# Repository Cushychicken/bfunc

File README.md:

# bfunc - An open source, breadboard friendly function generator

These are the source files for bfunc, a function generator I've been desiging, building, and programming in my spare time. 

The fastest way to understand what's going on here is to read [the design document](http://cushychicken.github.io/bfunc-design-doc/). That should give you a good top-level understanding of this project. If it doesn't, there's a Contact link on my blog. I encourage you to let me know if there's something you don't understand, or is otherwise unclear!

## Project Structure

All hardware files can be found in the `hardware/` directory. All hardware design was done using KiCAD. 

Software is broken into two directories: 

* `sw_embedded/` for all the code running on the bFunc board, and
* `sw_desktop/`, which contains the Python app for the GUI. 

The sw_embedded directory contains two subfolders:

* `stm32_cube_bfunc/` contains all the software used for building the prototype, which I made out of a STM32 BluePill board and a SparkFun Minigen Pro shield. 
* `bfunc_rev1/` contains all the software used in the first board revision. 

## Building the Project

This project uses GitHub Actions for automated building of the embedded firmware. The build process includes:

- **STM32F0 Firmware**: Builds the bfunc_rev1 firmware using ARM GCC toolchain
- **STM32F1 Firmware**: Builds the stm32_cube_bfunc firmware using ARM GCC toolchain

### Local Development

To build the embedded firmware locally, you'll need:

- ARM GCC toolchain for embedded development

Build commands:
```bash
# STM32F0 firmware
cd sw_embedded/bfunc_rev1
make clean
make all

# STM32F1 firmware  
cd sw_embedded/stm32_cube_bfunc
make clean
make all
```

## How can I contribute? 

I'm so glad you asked! Check out the [Call for Users](http://cushychicken.github.io/bfunc-call-for-users/) page on my blog. That will outline the next steps for getting a board, and getting yourself set up to work on it. 

After all that, if you _still_ can't get enough bFunc in your life - I've been keeping weekly project journals on my blog in addition to the design document. Here is a [link to the first one](http://cushychicken.github.io/bfunc-weekone-log/) to get you started.

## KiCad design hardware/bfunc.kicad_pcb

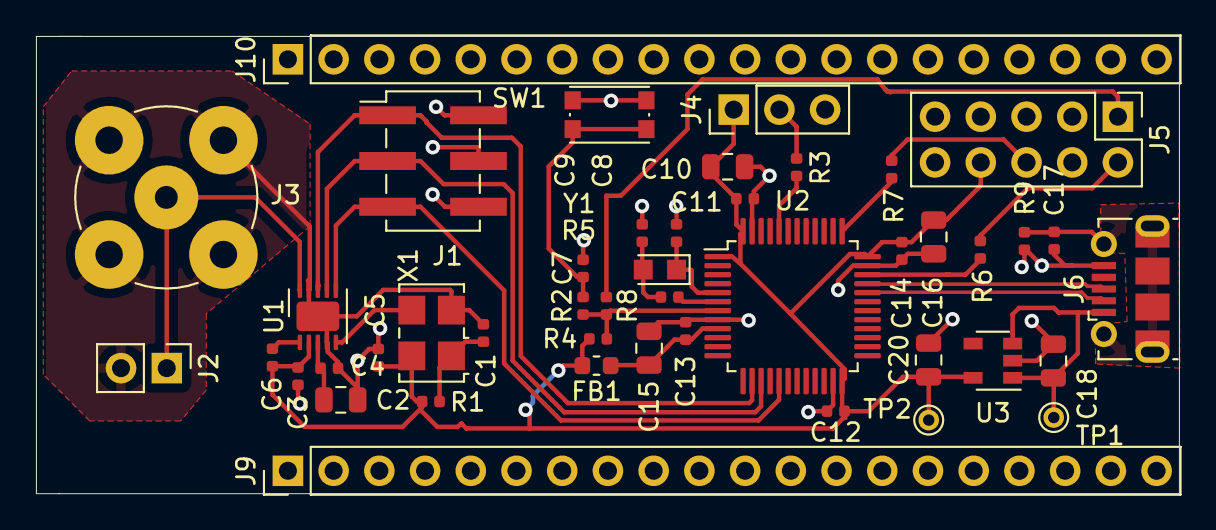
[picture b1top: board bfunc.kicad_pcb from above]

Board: 2 copper layers, 63.5 x 25.4 mm, 45 parts (0 on the bottom side), 27 nets.

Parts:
C1, C3, C4, C5, C11, C12, C14: 100nF; C_0402_1005Metric
C2: 10uF; C_0805_2012Metric
C6, C13: 10nF; C_0402_1005Metric
C7: 100pF; C_0402_1005Metric
C8, C9: 10pF; C_0402_1005Metric
C10, C16: 4.7uF; C_0805_2012Metric
C15, C18, C20: 1uF; C_0805_2012Metric
C17: 4.5nF; C_0402_1005Metric
FB1: Ferrite_Bead; L_0603_1608Metric
J1: Conn_02x03_Odd_Even; PinHeader_2x03_P2.54mm_Vertical_SMD
J2: Conn_01x02_Male; PinHeader_1x02_P2.54mm_Vertical
J3: Conn_Coaxial; BNC_TEConnectivity_1478204_Vertical
J4: Conn_01x03_Male; PinHeader_1x03_P2.54mm_Vertical
J5: Conn_02x05_Odd_Even; PinHeader_2x05_P2.54mm_Vertical
J6: USB_B_Micro; USB_Micro-B_Molex-105017-0001
J9, J10: Conn_01x20_Male; PinHeader_1x20_P2.54mm_Vertical
R1, R3: 10k; R_0402_1005Metric
R2: 330R; R_0402_1005Metric
R4: 2.2K; R_0402_1005Metric
R5: 390R; R_0402_1005Metric
R6, R7, R8: 0R; R_0402_1005Metric
R9: 1M; R_0402_1005Metric
SW1: SW_Push; SW_Push_1P1T_NO_CK_KMR2
TP1, TP2: TestPoint; PINTST
U1: AD9837; LFCSP-WD-10-1EP_3x3mm_P0.5mm_EP1.64x2.38mm
U2: STM32F072C8Tx; LQFP-48_7x7mm_P0.5mm
U3: MIC5504-3.3YM5; SOT-23-5
X1: SG-5032CAN; Oscillator_SMD_SeikoEpson_SG8002LB-4pin_5.0x3.2mm
Y1: Crystal; Crystal_SMD_TXC_9HT11-2pin_2.0x1.2mm_HandSoldering

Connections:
+3.3VA: C13.1, C15.1, FB1.1, U2.9
+3V3: C3.1, C5.1, C6.2, C10.1, C11.1, C12.1, C14.1, C16.1, C20.1, FB1.2, J4.1, J5.8, R1.1, R4.1, TP2.1, U1.2, U2.1, U2.24, U2.36, U2.48, U3.5, X1.4
+5V: C18.1, J6.1, TP1.1, U3.1, U3.3
/DDS Chip/AD9837_COMP: C6.1, U1.1
/DDS Chip/DDS_FSYNC: J1.1, U1.8, U2.14
/DDS Chip/DDS_MCLK: U1.5, X1.3
/DDS Chip/DDS_SCLK: J1.3, U1.7, U2.15
/DDS Chip/DDS_SDATA: J1.5, U1.6, U2.17
/DDS Chip/DDS_VCAP: C2.1, C4.1, U1.3
/DDS Chip/DDS_VOUT: J2.1, J3.1, U1.10
/DDS Chip/OSC_EN: C1.1, R1.2, X1.1
/MCU/BOOT_SW: R3.1, U2.44
/MCU/BOOT_SW_SEL: J4.2, R3.2
/MCU/OSC_IN: C8.1, U2.5, Y1.1
/MCU/OSC_OUT: R5.1, U2.6
/MCU/RESET_L: R2.1, R4.2, R8.2, U2.7
/MCU/RST_L_FLT: J5.1, R8.1
/MCU/SWCLK: R7.2, U2.37
/MCU/SWCLK_FLT: J5.6, R7.1
/MCU/SWDIO: R6.2, U2.34
/MCU/SWDIO_FLT: J5.2, R6.1
/MCU/USB_D_N: J6.2, U2.32
/MCU/USB_D_P: J6.3, U2.33
GND: C1.2, C2.2, C3.2, C4.2, C5.2, C7.2, C8.2, C9.2, C10.2, C11.2, C12.2, C13.2, C14.2, C15.2, C16.2, C17.1, C18.2, C20.2, J1.2, J1.4, J1.6, J2.2, J3.2, J4.3, J5.3, J5.4, J6.5, R9.1, SW1.1, U1.4, U1.9, U1.11, U2.8, U2.23, U2.35, U2.47, U3.2, X1.2
unnamed: C7.1, R2.2, SW1.2
unnamed: C9.1, R5.2, Y1.2
unnamed: C17.2, J6.6, R9.2

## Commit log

2020-01-30 bFunc: initial commit
2020-02-04 Broke cmpts into hierarchical design; swapped over to STM32 MCU (better USB reference examples, better toolchain support for my shitty old Mac)
2020-02-21 Uploaded STM32 configs, plus source code I'm working on for main.c
2020-02-21 Moved all Kicad stuff to /hardware/ directory
2020-02-24 Added .gitignore file
2020-02-24 Removed all of the build artifacts from git tracking
2020-02-24 Finished logic for setting control and frequency registers! And corresponding data structures
2020-02-25 Deleted file hardware/bfunc_layout.kicad_pcb; it was a scratch layout that wasn't in use.
2020-02-25 Finished Freq setting functions; Finished triangle wave generation; Added Phase setting functions
2020-02-28 Minor updates on PCB reviewed for re-fab at CircuitHub
2020-03-03 Basic USB functionality added - compiles and builds into a machine that switches between waveforms and also does USB loopback over virtual com port
2020-03-03 Bill of Materials for bFunc added in TSV format
2020-03-06 Started new port of code to STM32F072 MCU in bfunc_rev1/ directory; also implemented output selection based on CDC buffer contents
2020-03-06 Added README.md file
2020-03-08 Playing around with vim space/tab configs
2020-03-08 Started a simple GUI that can read in waveform types and frequency, then dump to command line.
2020-03-08 Added phase modifier window; made updates to command parsing function
2020-03-16 Added packet flagging to CDC_Receive_FS() callback funciton
2020-03-17 ProcessCommand() function now parses strings, and adds a nice little command line handle. Neat
2020-03-17 Added some more buttons and fields to the desktop application (push lags the actual work by a few days)
2020-03-21 Added pyserial functionality to desktop app; gets list of com ports from pyserial, uses that list to populate a dropdown list for selecting the serial port
2020-03-22 Updated the README.md to reflect the latest project directory structure; added a section on how to contribute
2020-03-22 Added PDF schematic to the hardware directory
2020-03-22 Updated .gitignore files
2020-03-22 Added .gdbinit file for bfunc_rev1 software
2020-03-22 DAC is now idle during IDLE state; big refactor of the command parsing and setting logic; added functionality to set frequency from the command line
2020-03-23 Added radiobuttons for selectingbetween waveform output or modulation output (modulation is still in development); refactored the link between button helper functions and buttons to no longer use the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
2020-03-24 Added sine, square, and triangle wave settings from command line.
2020-03-25 Updating KiCAD project file - had some slight updates after adding a PDF schematic
2020-03-25 Plumbed in phase0/phase1 setting functions
2020-03-25 Added function header comments to the AD9837 functions; deleted unused, commented out code
2020-03-25 Deleted extraneous command data structure; was not used anywhere in code
2020-03-26 Updated character handling to deal with Backspaces on Mac terminals, which are actually Deletes
2020-03-27 Updated USB Product String to a custom one that says device is a bFunc
2020-03-27 Refactored main loop to copy buffer from UserRxBufferFS to cmd_buffer, while simultaneously processing those results
2020-03-27 Plumbed in freq0, freq1, phase0, phase1 settings behind the Tkinter buttons
2020-03-28 Fixed multiplying factors for frequency and phase settings
2020-03-28 initialize frequency and phase registers to a known state on startup
2020-04-02 Added STCubeMX codegen bracket comments back - needed for quick peripheral inits while not trashing prewritten code
2020-04-02 Changed position of usb_packet_flag declaration so it's not erased by future runs of STCubeMX
2020-04-02 Updated HAL init file that initializes TIM2 instead of TIM1
2020-04-02 Updates to main.c generated by STCubeMX to init TIM2 instead of TIM1
2020-04-02 Includes changes to STCubeMX project init file
2020-04-02 Added in serial handling for sawtooth waves; also added in AD9837 state settings for sawtooth waves
2020-04-03 Added command handling/state machine to enter sawtooth mode; still need to coordinate switching between phase0/phase1 registers for managing phase offset of accumulator
2020-04-06 Added GNU Build ID support to Makefile and linker script
2020-04-06 Updated .gitignore
2020-04-06 Updated .gitignore to ignore .lst files in /build/ directory
2020-04-06 Added QA test script for testing outgoing boards.
2020-04-06 Updated .gitignore to ignore Mac .DS_Store files
2020-04-07 Added GNU build ID functionality to software; deleted *.lst and *.bin files from git tracking
2020-04-08 Used STM32MXCube to generate TIM2 interrupt settings; wrote some code to toggle an IO as proof of GPIO life
2020-04-15 Enabled bootloader support
2020-04-28 Deleted HW .sch-bak and .kicad_pcb-bak files. Added to .gitignore so future commits won't add them back.
2020-05-04 Updated .gdbinit to use OpenOCD for debugging; added openocd.cfg file
2020-05-04 Added serial commands to qa test script
2020-05-05 Simplified openocd.cfg file
2020-05-05 Added ToggleFreqRegister function to switch between freq0 and freq1
    Formatting cleanup
    Fixed a bug in SetFreq1Value - improperly masked to freq0 register
2020-05-05 Updated out_qatest.py to have better python3 compatibility, as well as determining linux vs mac for serial console file handle format. Also finalized automating bfunc output via serial port.
2020-05-06 Added TogglePhaseReg() function to swap between phase0 and phase1 register values being applied to output. Added phasesel command to call TogglePhaseReg().
2020-05-06 Finally fixed erroneous backspace/delete handling. The virtual com port console will now do proper backspacing!
2020-05-06 Added waveform mode MOD_PSK to handle binary phase shift keying states.
    Added stub function SetSymbolRate() to set symbol interval for MOD_PSK.
    Will be filled in later with TIM2 settings to handle modulations.
    Added StopOutput() at the start of main(), before superloop, to reset DAC
    output on startup. Changed SetFreq0Value() and SetFreq1Value() to init to
    0x00000000.
2020-05-07 Finished SetSymbolRate() function, which sets up TIM2 to fire an ISR at millisecond intervals.
    Finished StopModulation() function, which disables TIM2 by clearing the CEN
    bit.
    Binary phase shift keying example is complete. Needs a bit of refining on
    keying interval. Ex call: `mod_bpsk <freq> <symbol_int>`
2020-09-21 Initial commit of for version 2
2020-09-21 Updated .gitignore to ignore contents of sw_rtl/tmp
2021-07-07 Updated desktop app to work with Python 3
2023-02-23 Addex extern to buffer declaration to avoid multiple declarations
2025-10-23 Updated README and added requirements.txt
2025-10-23 Added github actions build workflow
2025-10-23 Refactored to write out separate ad9837 driver, command parser, and wfm controller
2025-10-23 Disabled deprecated STM32F1 build step; added git describe info
2025-10-23 Added GIT_VERSION info into makefile and codebase
2025-10-23 Made git describe info available to github actions job
2025-10-23 complete git describe info
